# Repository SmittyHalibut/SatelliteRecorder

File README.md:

# SatelliteRecorder
An audio router/mixer to connect an HT with "Kenwood" speaker mic pinout, a PC (eg: gaming) headset, and a phone (eg: iPhone) to make working and recording Amateur Radio FM Satellites easier.

## THIS DESIGN IS PROBABLY BROKEN!!!
People have asked me to post this file, so I am.  But I do not claim it works perfectly.  It PROBABLY works pretty well, but I can't guarantee anything.  There are almost certainly improvements that can, and should be made.

If you're downloading this, do a `git log`.  If you only see one or two commits from me talking about "initial commit" or "warning!" or whatever, you probably don't want to just build this without reviewing it and making sure you understand what you're building first.

## The Idea
The goal was to build a device that routes audio to and from:
* An HT. I have an AnyTone 868, which has the "Kenwood Standard" speaker mic connection that so many radios use, so that's what this is. Use a straight through 3.5mm male to male cable, and a straight through 2.5mm male to male cable between the "Radio" ports on this board and your HT.  If you have an HT with a different pin out, you're on your own.
* A Headset.  PC gaming head sets are common, cheap, and can interface with radios pretty easily.  Electret mics, dynamic headphones, etc. Easy peasy. And they're cheap.
* A phone.  I use an iPhone, but I think the 4 pin 3.5mm TRRS connector is pretty standard.  Of course, iPhones don't HAVE this connector anymore, but the Lightning to 3.5mm headphone jack dongles work fine.
  * Tip: Left speaker audio 
  * Ring 1: Right speaker audio.
  * Ring 2: Shield and common ground.
  * Sleeve: Mic audio.
* A remote PTT button, probably mounted on the handle of your antenna.

Audio is routed and mixed in what I consider to be "ideal" ways:
* Receive audio from the radio goes to your headphones, and the mic input to the phone so it can be recorded.
* Mic audio from your headset goes to the radio for transmit, and is mixed and set to the mic input to the phone so it is recorded too.
* Speaker audio from the phone is mixed and set to your headhpones too.  So you can hear both the radio, and play-back audio from the phone.

This way, you can record the whole pass, both your audio and the receive audio.  And you can hear play-back from your phone without having to change anything.

That's about all the support I'm going to give on it right now. If you have any questions or want to discuss it with me, find me on Twitter: @SmittyHalibut.

Good luck!  And let me know if you do anything useful with it!

73 de KR6ZY
-Mark

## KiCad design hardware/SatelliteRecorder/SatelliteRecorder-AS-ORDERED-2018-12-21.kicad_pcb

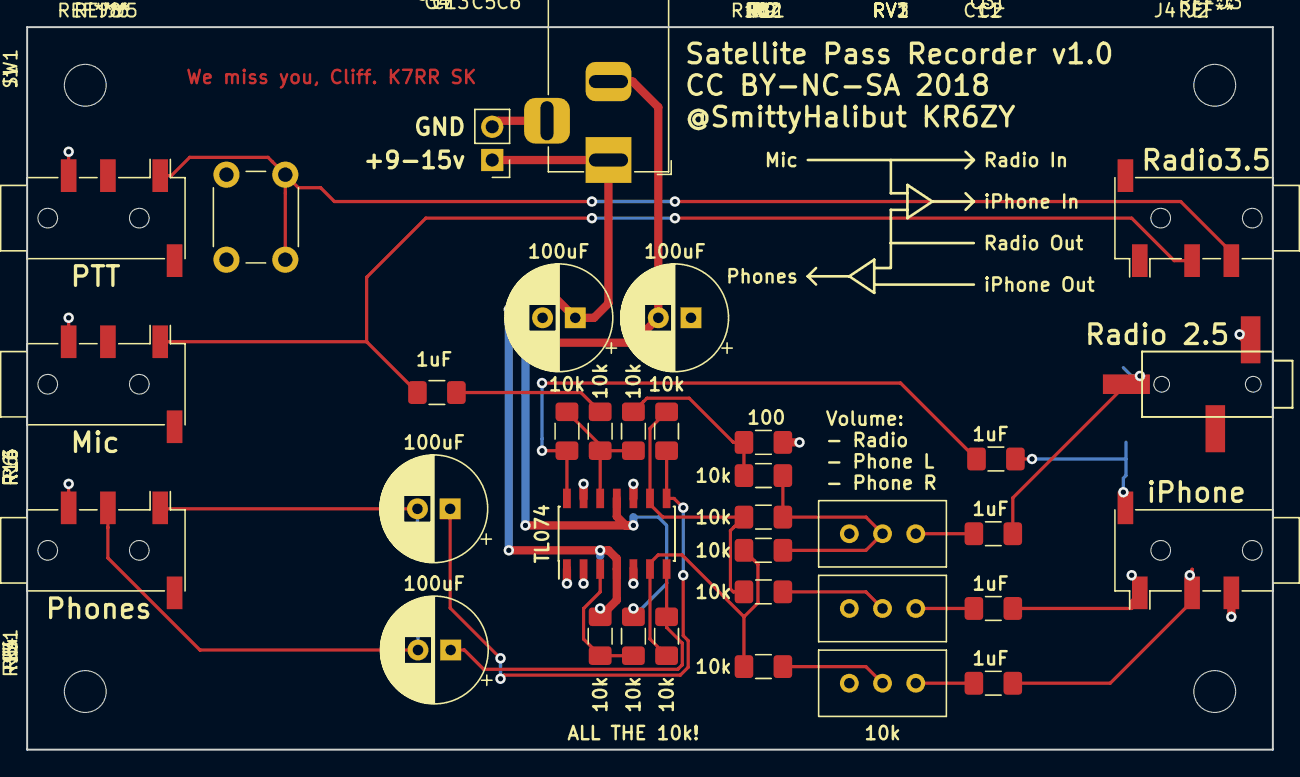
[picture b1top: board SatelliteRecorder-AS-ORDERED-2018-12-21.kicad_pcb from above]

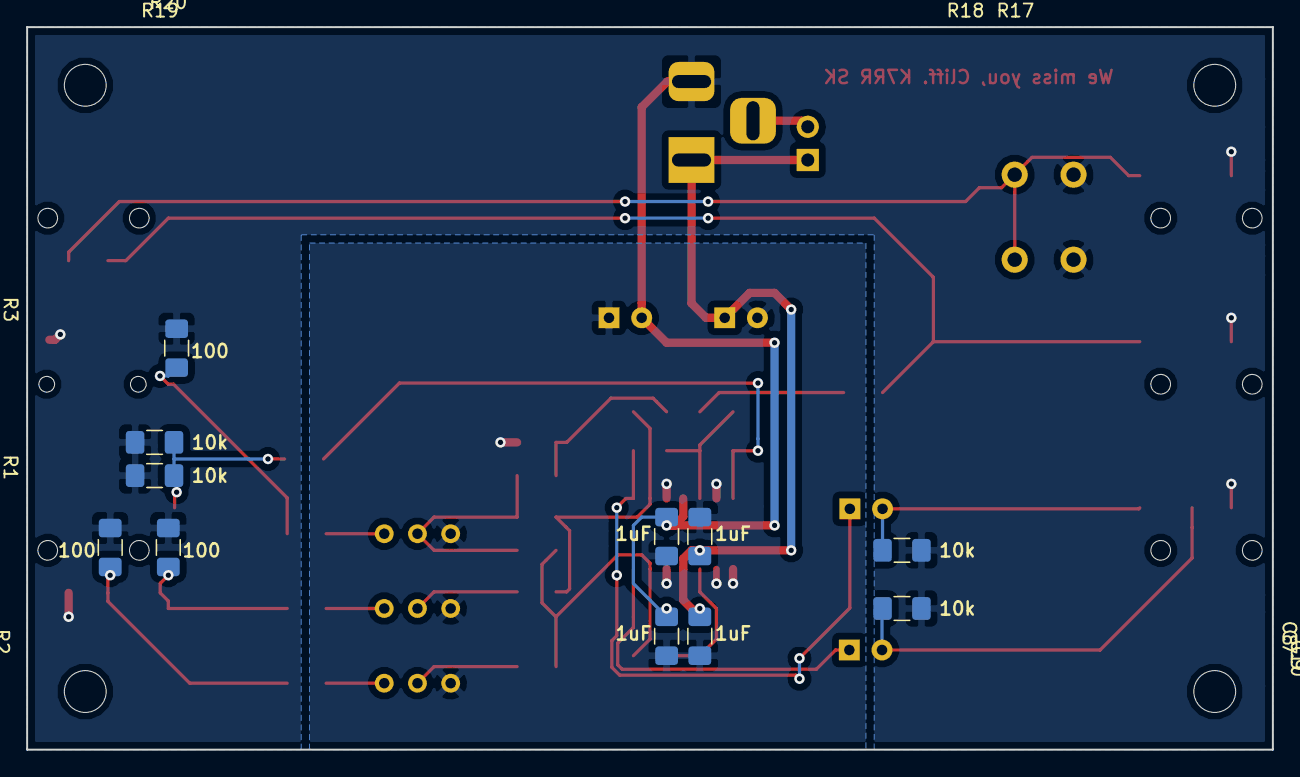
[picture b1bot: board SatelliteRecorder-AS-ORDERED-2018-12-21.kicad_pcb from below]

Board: 2 copper layers, 95.2 x 55.2 mm, 46 parts (11 on the bottom side), 27 nets.

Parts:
C1, C2, C3, C4, C7, C8, C11: 1uF; C_1206_3216Metric_Pad1.42x1.75mm_HandSolder
C5, C6, C12, C13: 100uF; CP_Radial_D8.0mm_P2.50mm
C9, C10: .1uF; C_1206_3216Metric_Pad1.42x1.75mm_HandSolder
J1: Power In; BarrelJack_Horizontal
J2: iPhone; Jack_3.5mm_PJ320D_Horizontal
J3: Radio 2.5mm; PJ-208
J4: Radio 3.5mm; Jack_3.5mm_PJ320D_Horizontal
J5: Headphones; Jack_3.5mm_PJ320D_Horizontal
J6: Mic; Jack_3.5mm_PJ320D_Horizontal
J7: Internal Power; PinHeader_1x02_P2.54mm_Vertical
J8: PTT; Jack_3.5mm_PJ320D_Horizontal
R1, R2, R3, R12: 100; R_1206_3216Metric_Pad1.42x1.75mm_HandSolder
R4, R5, R6, R7, R8, R9, R10, R11, R13, R14, R15, R16, R17, R18, R19, R20: 10k; R_1206_3216Metric_Pad1.42x1.75mm_HandSolder
RV1, RV2, RV3: 10k; Potentiometer_Bourns_3296W_Vertical
SW1: PTT; SW_PUSH_6mm
U1: TL074; SOIC-14_3.9x8.7mm_P1.27mm

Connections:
BusLeft: R7.1, R9.1, R14.2, U1.9
BusMic: R6.1, R13.1, R16.2, U1.12
BusRight: R8.1, R10.1, R15.2, U1.6
GNDS: C5.2, C6.1, C7.2, C8.1, C9.2, C10.1, R12.1, RV1.3, RV2.3, RV3.3, U1.1, U1.2, U1.5, U1.10, U1.13
HeadsetGND: C6.2, C8.2, C10.2, J1.2, J2.S, J3.S, J5.S, J6.S, J8.S, R1.2, R2.2, R3.2, R5.2, R17.1, R18.1, R19.1, R20.1, SW1.1, U1.11
HeadsetLeft: C12.2, J5.T, R17.2
HeadsetMic: C4.2, J4.R1, J6.T
HeadsetRight: C13.2, J5.R1, R18.2
unnamed: C1.1, RV1.1
unnamed: C2.1, RV2.1
unnamed: C3.1, RV3.1
unnamed: C4.1, R6.2
unnamed: C11.2, R16.1, U1.14
unnamed: C12.1, R14.1, U1.8
unnamed: C13.1, R15.1, U1.7
unnamed: J1.3, J7.2
unnamed: R4.2, R5.1, U1.3
unnamed: R7.2, RV1.2
unnamed: R8.2, RV2.2
unnamed: R9.2, R10.2, R11.2, RV3.2
unnamed: R11.1, R12.2, R13.2
PhoneLeft: C1.2, J2.T, R1.1
PhoneMic: C11.1, J2.R2, R19.2, R20.2
PhoneRight: C2.2, J2.R1, R2.1
RadioPTT: J4.S, J8.T, SW1.2
RadioSpk: C3.2, J3.T, R3.1
VCC: C5.1, C7.1, C9.1, J1.1, J7.1, R4.1, U1.4

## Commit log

2019-09-08 Initial commit. Be sure to read the README for warnings about this design!

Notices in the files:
hardware/SatelliteRecorder/SatelliteRecorder-AS-ORDERED-2018-12-21.kicad_pcb:
CC BY-NC-SA 2018
